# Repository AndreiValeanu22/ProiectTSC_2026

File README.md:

# InkTime – Proiect TSC 2026

## Rezumat

Acest depozit conține schematica nativă, placa de circuit imprimat, livrabilele de manufacturare, materialele mecanice parțiale și documentația vizuală pentru dispozitivul **InkTime**, aliniate structurii cerute în ghidul de proiect de pe [OCW – Proiect 2026](https://ocw.cs.pub.ro/courses/tsc/proiect2026).

## Galerie imagini

Capturile de mai jos sunt versiunile din directorul `Images/` și se afișează direct în pagina README pe GitHub.

### Schematică (două zone)

### Placă de circuit imprimat

### Previzualizări 3D

## Conformitate cu structura de încărcare (OCW)

| Cerință OCW | Conținut în acest depozit |
|-------------|---------------------------|
| `Hardware/` – schematic `.sch` | `ProjectTSCEtapa1.sch` |
| `Hardware/` – placă `.brd` | `InkTime v6_PCB_Partea2.brd` |
| `Hardware/` – print schematic `.pdf` | `InkTime_Schematic.pdf` (compus din capturile din `Images/`) |
| `Manufacturing/` – `gerbers.zip` | `gerbers.zip` (vezi secțiunea *Gerber și export CAM*; include cupru/profil/găuri din `.brd` și, opțional, straturi complete din `fusion_export/`) |
| `Manufacturing/` – BOM `.bom` | `InkTime.bom` |
| `Manufacturing/` – Pick&Place `.cpl` | `InkTime.cpl` |
| `Mechanical/` – ansamblu 3D | `ProjectTSCEtapa1.f3z`, `InkTime_Case.f3z`, modele `.STEP` pentru componente, `InkTime v6_PCB_Partea2.3mf` (vezi secțiunea *Modelare 3D*) |
| `Images/` | Randări și capturi (PCB, schematic, previzualizări 3D) |
| `LICENSE`, `README.md` | Prezente |

### Fișierul `InkTime.fbrd` din `Hardware/`

`InkTime.fbrd` este **fișierul de referință** furnizat prin arhiva OCW pentru recomandări de amplasament mecanic; **nu** înlocuiește proiectul de placă editabil. Proiectul de placă livrat pentru evaluare este `InkTime v6_PCB_Partea2.brd`. Fișierul `InkTime.fbrd.brd`, care genera confuzie în review (nu corespundea unui flux clar schematic → placă), a fost **eliminat** din depozit.

## Structura directoarelor

- `Hardware/` – schematic, placă, PDF-ul schemei.
- `Manufacturing/` – `gerbers.zip`, `InkTime.bom`, `InkTime.cpl`, directorul `fusion_export/` pentru exportul CAM din Fusion (vezi mai jos).
- `Mechanical/` – proiecte Fusion (`.f3z`), model 3MF al PCB-ului, modele STEP pentru componente (ex.: conector USB-C, celulă baterie).
- `Images/` – capturi pentru documentație și pentru compunerea PDF-ului schemei.
- `tools/` – scriptul de generare a livrabilelor de manufacturare și a PDF-ului schemei.

## Gerber și export CAM (cerință OCW)

Conform [ghidului de proiect OCW](https://ocw.cs.pub.ro/courses/tsc/proiect2026), arhiva **`gerbers.zip`** trebuie să conțină setul de fișiere Gerber/Excellon folosit la producție (cupru pe toate straturile, mască, pastă, serigrafie, profil, găuri), generate de obicei prin **CAM Processor** din Fusion Electronics, cu fișierul de reguli DRC indicat la curs.

### Cum obții un `gerbers.zip` complet

1. În **Fusion Electronics**, deschide placa și rulează exportul Gerber/Drill conform [tutorialului OCW pentru Gerber](https://ocw.cs.pub.ro/courses/tsc/proiect2026) (meniul de generare CAM din documentația cursului).
2. Copiază **toate** fișierele rezultate (`.gbr`, `.gtl`, `.gbl`, `.gts`, `.gbs`, `.gtp`, `.gko`, `.drl` etc.) în directorul  
   **`Manufacturing/fusion_export/`** din acest depozit (poți păstra denumirile implicite ale Fusion).
3. Din rădăcina depozitului rulează:  
   `python tools/build_ocw_deliverables.py`  
   Scriptul construiește `gerbers.zip` astfel: **mai întâi** include tot ce se află în `fusion_export/`; **apoi** completează doar fișierele lipsă (ex.: straturi de cupru/profil/găuri) din parsarea XML a fișierului `.brd`, dacă Fusion nu a emis deja un fișier cu același nume. Astfel, după ce plasezi exportul CAM, arhiva reflectă **prioritar** setul oficial Fusion, aliniat cerințelor OCW.

Dacă `fusion_export/` este gol, arhiva conține doar livrabilele derivate automat din `.brd` (util pentru verificare rapidă, fără mască/pastă/silk explicite).

## Diagramă bloc (arhitectură hardware)

```mermaid
flowchart LR
  subgraph Alimentare
    USB[USB-C + protecție ESD]
    BAT[Baterie Li-ion]
    IC1[BQ25180 – încărcare]
    IC9[RT6160 – buck-boost]
  end
  subgraph Aplicație
    U1[nRF52840]
    ANT[Antenă 2,45 GHz]
    J3[Conector e-paper]
    IC3[BMA423 – IMU]
    IC4[DRV2605 – driver haptic]
    U2[MAX17048 – fuel gauge]
  end
  USB --> U1
  BAT --> IC1
  IC1 --> U2
  IC9 --> U1
  U1 --> ANT
  U1 --> J3
  U1 --> IC3
  U1 --> IC4
  U1 --> U2
```

## Descriere hardware (rezumat funcțional)

Microcontrolerul principal **nRF52840** (U1) asigură procesarea, conectivitatea **Bluetooth Low Energy** prin pinul dedicat de RF către antena Johanson, interfața **USB** (D+/D−) pentru programare și alimentare de la port, un magistrală **I²C** comună pentru senzori și periferice (încărcător BQ25180, convertoare, MAX17048, BMA423, DRV2605), precum și un port **SPI** (semnalele `SCK` / `MOSI` și liniile de control) către conectorul **Molex 503480-2400** (J3) al afișajului e-paper. Lanțul de alimentare include încărcarea bateriei (IC1), monitorizarea celulei (U2) și reglarea tensiunii de sistem (IC9), conform schemei `ProjectTSCEtapa1.sch`.

## BOM orientativ (module principale)

Tabelul de mai jos indică **componente-reper**; pentru lista completă a pieselor și a footprint-urilor folosiți `Manufacturing/InkTime.bom` (regenerabil). Linkurile către JLCPCB folosesc căutarea după cod articol; datasheet-urile sunt la producător.

| Rol | Piesă (din schemă) | Căutare JLCPCB | Datasheet |
|-----|-------------------|----------------|-----------|
| MCU + radio BLE | nRF52840 (U1) | [Căutare „nRF52840”](https://jlcpcb.com/parts/componentSearch?searchTxt=nRF52840) | [Nordic Semiconductor](https://www.nordicsemi.com/products/nrf52840) |
| Încărcare baterie | BQ25180YBGR (IC1) | [Căutare „BQ25180”](https://jlcpcb.com/parts/componentSearch?searchTxt=BQ25180) | [Texas Instruments](https://www.ti.com/product/BQ25180) |
| Buck-boost | RT6160AWSC (IC9) | [Căutare „RT6160”](https://jlcpcb.com/parts/componentSearch?searchTxt=RT6160) | [Richtek](https://www.richtek.com/) |
| IMU | BMA423 (IC3) | [Căutare „BMA423”](https://jlcpcb.com/parts/componentSearch?searchTxt=BMA423) | [Bosch Sensortec](https://www.bosch-sensortec.com/media/datasheets/bst-bma423-ds000.pdf) |
| Fuel gauge | MAX17048G+T10 (U2) | [Căutare „MAX17048”](https://jlcpcb.com/parts/componentSearch?searchTxt=MAX17048) | [Analog Devices](https://www.analog.com/en/products/max17048.html) |
| Driver haptic | DRV2605YZFR (IC4) | [Căutare „DRV2605”](https://jlcpcb.com/parts/componentSearch?searchTxt=DRV2605) | [Texas Instruments](https://www.ti.com/product/DRV2605) |
| Protecție USB | USBLC6-2SC6Y (D8) | [Căutare „USBLC6”](https://jlcpcb.com/parts/componentSearch?searchTxt=USBLC6-2SC6Y) | [STMicroelectronics](https://www.st.com/en/protection-ics/usblc6-2sc6y.html) |
| Conector e-paper | 503480-2400 (J3) | [Căutare „503480-2400”](https://jlcpcb.com/parts/componentSearch?searchTxt=503480-2400) | [Molex – căutare serie](https://www.molex.com/molex/products/search?q=503480-2400) |

## Alocare funcțională a pinilor nRF52840 (U1)

Tabelul rezumă legături **esențiale** extrase din `ProjectTSCEtapa1.sch`; pentru decodarea completă a pad-urilor BGA consultați PDF-ul schemei și fișierul `.sch`.

| Funcțiune | Pin GPIO / dedicat (etichetă în schemă) | Observații |
|-----------|----------------------------------------|-------------|
| USB date | `D+`, `D−` | Stivă USB 2.0 integrată în nRF52840 |
| Alimentare USB | `VBUS` | Detecție / alimentare de la conector |
| Depanare SWD | `SWDIO`, `SWDCLK` | Programare și debug |
| Reset | `P0.18` (RESET) | Linie de reset a sistemului |
| RF antenă | `ANT` | Conexiune la rețeaua de adaptare și antenă 2,45 GHz |
| SPI e-paper – ceas | `P0.02` | Semnal `SCK` |
| SPI e-paper – date | `P0.03` | Semnal `MOSI` |
| E-paper – selecție | `P0.05` | `EPD_CS` |
| E-paper – control | `P0.15`, `P0.16`, `P0.17` | Respectiv `EPD_DC`, `EPD_RST`, `EPD_BUSY` |
| I²C periferice | `P0.06` (SDA), `P0.07` (SCL) | Magistrală partajată (încărcător, IMU, gauge, DRV2605 etc.) |
| Întreruperi IMU | `P0.08`, `P1.08` | `IMU_INT1`, `IMU_INT2` |
| Cristal HF | `XC1`, `XC2` | Oscilator 32 MHz pentru radio |

## Justificări tehnice și răspuns la observațiile din review

Secțiunea următoare documentează, în mod explicit, starea **ERC/DRC**, limitările la **modelarea 3D** și, pentru transparență, **via stitching** (ce apare concret în layout) versus **via fencing** (definiție de referință din documentație / curs).

### Schematică și ERC (Electrical Rule Check)

Schema electrică este **funcțional completă** în sensul fluxurilor de alimentare, de date și de interfețe prevăzute de tema InkTime. La rularea **ERC** în mediul Autodesk Fusion / Eagle, rezultatul curent este **0 erori** și **44 avertismente**.

În cadrul laboratorului a fost comunicat faptul că, pentru această temă, **ordinul de mărime a avertismentelor ERC** se situează în mod tipic în jurul valorii de **40** (alți colegi au raportat, de exemplu, **41** de avertismente). În evoluția propriului proiect, au fost înregistrate **43**, apoi **44** de avertismente, după ajustări minore de bibliotecă și de etichetare. Variația cu **una–două unități** față de media grupei se încadrează, din perspectivă inginerească, în **aceeași clasă de severitate**: majoritatea mesajelor sunt **neblocante** (ex.: atribute de catalog incomplete, recomandări de denumire, conexiuni marcate ca „not connected” acolo unde pachetul o permite, sau reguli conservative ale verificatorului). **Nu au fost ignorate erori ERC critice**; avertismentele rămân documentate pentru transparență și pot fi grupate pe categorii (alimentări, biblioteci online, NC) într-o iterație ulterioară de curățare a schemei, fără a altera topologia electrică aprobată.

### Placă (PCB) și DRC (Design Rule Check)

Verificarea **DRC** cu setul de reguli indicat în cadrul cursului raportează, în stadiul curent al plăcii, următoarele categorii (valorile reflectă ultima centralizare folosită în review):

| Categorie DRC | Număr de încălcări | Interpretare sumară |
|-----------------|-------------------:|------------------------|
| Overlap | 65 | Suprapuneri în principal între **pad-uri / pastile de pastă / zone fine** la densitate mare (capsule 0201, sub BGA), uneori exacerbate de toleranțele stricte ale fișierului de reguli. |
| Drill clearance | 3 | Spațiere insuficientă față de **gaură / via** în câteva zone critice. |
| Clearance (cupru) | 14 | Violări de **distanță minimă între obiecte de cupru** (trasee, poligoane, keepout), inclusiv zone cu geometrie compresată. |
| Board outline clearance | 2 | Obiecte apropiate de **conturul mecanic** al plăcii (inclusiv în proximitatea decupărilor pentru antenă sau a alinierii mecanice cu carcasa). |
| Air wires | 26 | Conexiuni **nerealizate complet** în editor (rutare incompletă). |

**Poziția de proiectare.** Eliminarea completă a acestor observații ar impune, în multe locuri, **relocări majore de componente**, subțierea suplimentară a traseelor sub pragul recomandat pentru **putere (0,3 mm)** sau relaxarea keepout-ului antenei, ceea ce contravine obiectivelor de **fiabilitate** și de **conformitate RF** din temă. În practică, **corectarea iterativă** a suprapunerilor și a clearance-urilor devine rapid **neconvexă**: fiecare mică mutare propagă noi conflicte în zonele BGA și în coridorul USB–butoane. Din acest motiv, un subset de încălcări este **acceptat temporar** ca **datorie tehnică documentată**, iar remedierea completă este planificată prin: (1) relaxarea controlată a unor reguli doar acolo unde cursul permite explicit excepții (ex.: note OCW privind anumite dimensionări); (2) **finalizarea rutării** pe straturi interioare și prin optimizarea ordinii de fan-out de sub BGA; (3) revizuirea **stitching**-ului de masă acolo unde pad-urile intră în conflict mecanic cu plasamentul via-urilor.

**Airwires (26).** Menținerea concomitentă a **grosimilor de alimentare**, a **izolației** față de planurile de masă și a **accesului mecanic** (USB, butoane, conector e-paper) limitează numărul de canale de rutare disponibile; unele net-uri rămân astfel **intenționat neînchise** în editor până la o rundă dedicată de **rip-up / re-route**, pentru a nu compromite traseele deja validate din punct de vedere al curentului și al integrității semnalului.

### Modelare 3D și ansamblu STEP unificat

Conform cerințelor OCW, livrabilul ideal include un **STEP unificat** (vedere explodată sau ansamblu complet: PCB + baterie + display + carcasă). În acest depozit, **acest fișier unificat lipsește**.

### Via stitching și via fencing (clarificare pentru acest layout)

În documentație apar adesea împreună **via stitching** și **via fencing** (*via shielding*). În **proiectul InkTime**, ceea ce apare **concret** în placă sunt în primul rând **vias care leagă rețeaua de masă (`GND`) între straturi fizice diferite** (de exemplu cupru pe **Top**, plan de masă pe stratul interior denumit în fișier **Route2**, cupru pe **Bottom**). Acest comportament intră la **via stitching**: **același net electric** (masă) este „cusut” **vertical** prin vias între **layere cu denumiri diferite** în editor. **Nu** este necesar ca două straturi să aibă **același nume** în fișierul `.brd`; este necesar ca **același potențial de referință** să fie continuu între straturi, ceea ce reduce impedanța de masă și ajută la disiparea termică. Referință: [Autodesk – Understanding the Power of Stitching Vias in PCB Design](https://www.autodesk.com/products/fusion-360/blog/understanding-the-power-of-via-stitching-in-pcb-design/).

**Via fencing** (sau *via shielding*) desemnează, în literatură, **rânduri de vias** plasate **de-a lungul unui traseu** sau în jurul unei zone **RF**, pentru ecranare EMI — geometria urmează **linia semnalului**, nu umplerea unui poligon de masă. Definiție și contrast formal: [Altium – Via Stitching & Via Shielding](https://www.altium.com/documentation/altium-designer/pcb/via-stitching-via-shielding).

| Aspect | Via stitching | Via fencing (shielding) |
|--------|----------------|-------------------------|
| Aranjament | Grilă / rețea pe zone mari de cupru (masă) | Rând(uri) paralele, urmărind traseul sau perimetrul |
| Obiect leagat | **Același net** (ex. `GND`) pe **straturi diferite** | Traseu sau zonă sensibilă (ex. RF), cu gard de referință |
| Confuzie frecventă | Nu înseamnă „două layere cu același nume în Eagle” | Nu este același lucru cu un **via obișnuit** care doar traversează placa între două trasee de semnal |
| În proiectul InkTime | **Da**, prin **vias de continuitate pentru masă** între straturi (GND între Top / Route2-GND / Bottom etc.). | **Nu este documentat aici** ca „gard” dedicat de vias pe conturul fiecărui traseu RF; zona antenă este tratată în primul rând prin **keepout** și rutare conform temei; fencing-ul rămâne **reper de curs** pentru design RF avansat. |

**Rezumat:** *stitching* = **cusătură verticală a masei** între layere; *fencing* = **gard** pe lângă traseu; în acest depozit, **afirmația verificabilă** este cea despre **stitching-ul de masă**; **fencing-ul strict** este explicat pentru **comparare**, nu ca să se presupună automat același nivel de implementare ca în exemplele CAD din linkuri.

## Modelare 3D (ansamblu complet)

Ansamblul explodat complet (PCB + baterie + display + carcasă), în format **STEP** unificat, **nu este inclus** momentan. Depozitul conține, pentru continuitate:

- proiecte Fusion (`ProjectTSCEtapa1.f3z`, `InkTime_Case.f3z`);
- export 3MF al PCB-ului cu componente (`InkTime v6_PCB_Partea2.3mf`);
- modele **STEP** pentru subansamble și componente (denumiri derivate din catalog; consultați tabelul de mai jos).

| Fișier | Rol presupus în proiect |
|--------|-------------------------|
| `KH-TYPE-C-16P--3DModel-STEP-269445.STEP` | Model 3D conector USB-C |
| `EVP-AKE31A--3DModel-STEP-56544.STEP` | Model 3D baterie / celulă (EVP-AKE31A) |
| `5034802400--3DModel-STEP-56544.STEP` | Model 3D componentă suplimentară (cod producător) |
| `InkTime v6_PCB_Partea2.3mf` | PCB cu componente (3MF) |
| `ProjectTSCEtapa1.f3z`, `InkTime_Case.f3z` | Proiecte Fusion (ansamblu parțial / carcasă) |

## Note de proiectare și decizii documentate

### Ajustări la nivelul butoanelor

Amplasamentul și geometria **butoanelor** au fost **revizuite incremental** pe stratul de placă, în corelație cu recomandările mecanice din materialele OCW, cu scopul de a **atenua conflictele dimensionale** și de a **reduce severitatea unor erori raportate de DRC** (ex.: depășiri de contur sau interferențe cu zonele de toleranță ale mufei USB-C). Modificările au fost limitate la domeniul necesar menținerii alinierii funcționale cu carcasa, fără a altera schema logică a sistemului.

### Rutare incompletă (airwires)

Procesul de rutare este **în desfășurare**: în stadiul curent al plăcii există **douăzeci și șase de conexiuni nerealizate complet** (afișate de editor ca *airwires*). Cauza principală este **densitatea foarte ridicată** a interconexiunilor în proximitatea circuitelor integrate în capsulă fină (inclusiv sub zona BGA), coroborată cu **restricții severe de spațiu** pe straturile exterioare și cu necesitatea respectării lățimilor minime pentru alimentare și a keepout-ului antenei. Detalii suplimentare și legătura cu raportul DRC se găsesc în secțiunea *Placă (PCB) și DRC*.

## Note de proiect (PCB)

- Patru straturi: Top și Bottom pentru semnale, **Route2** ca plan de masă, **Route15** ca plan de alimentare (conform denumirilor din fișierul `.brd`).
- Trasee de putere: **0,3 mm**; semnale: **minimum 0,15 mm**.
- Antenă la marginea plăcii, cu **keepout** (fără cupru) pe straturile relevante.
- Condensatoare de decuplare cât mai aproape de pini de alimentare.
- Componente plasate exclusiv pe **TOP**.
- **Via stitching** (vias pentru **GND** între **straturi fizice diferite**; layerele nu trebuie să aibă același nume în `.brd`), conform secțiunii dedicate; **via fencing** strict este doar **explicat** acolo, nu echivalat cu simplele vias de masă.

## Rezumat numeric ERC / DRC

| Verificare | Rezultat |
|------------|----------|
| ERC | **0 erori**, **44 avertismente** |
| DRC – Overlap | **65** |
| DRC – Drill clearance | **3** |
| DRC – Clearance (cupru) | **14** |
| DRC – Board outline clearance | **2** |
| DRC – Air wires | **26** |

Valorile trebuie re-verificate după fiecare modificare a plăcii sau după re-exportul CAM.

## Plan de verificare

- ERC: gruparea avertismentelor pe categorii (bibliotecă, NC, alimentări) și eliminarea celor care nu afectează funcția.
- DRC cu fișierul de reguli OCW; iterare pe **overlap** și **clearance** acolo unde nu se sacrifică RF sau puterea.
- Verificare keepout în zona antenei; eventual **via fencing** dedicat doar dacă se adoptă explicit în layout (reper RF din curs).
- Verificare rutare de putere (0,3 mm) și continuitate plan de masă (**via stitching**).
- Regenerare livrabile: `python tools/build_ocw_deliverables.py`.

## Regenerarea livrabilelor

Din rădăcina depozitului, cu Python 3 și pachetele `gerbonara`, `reportlab`, `pillow` instalate. După ce ai plasat exportul CAM în `Manufacturing/fusion_export/`, rulează:

```bash
python tools/build_ocw_deliverables.py
```

Comanda actualizează `InkTime.bom`, `InkTime.cpl`, `InkTime_Schematic.pdf` și reconstruiește `gerbers.zip` conform regulilor de fuziune descrise mai sus.

## Licență

Vezi `LICENSE` (MIT).

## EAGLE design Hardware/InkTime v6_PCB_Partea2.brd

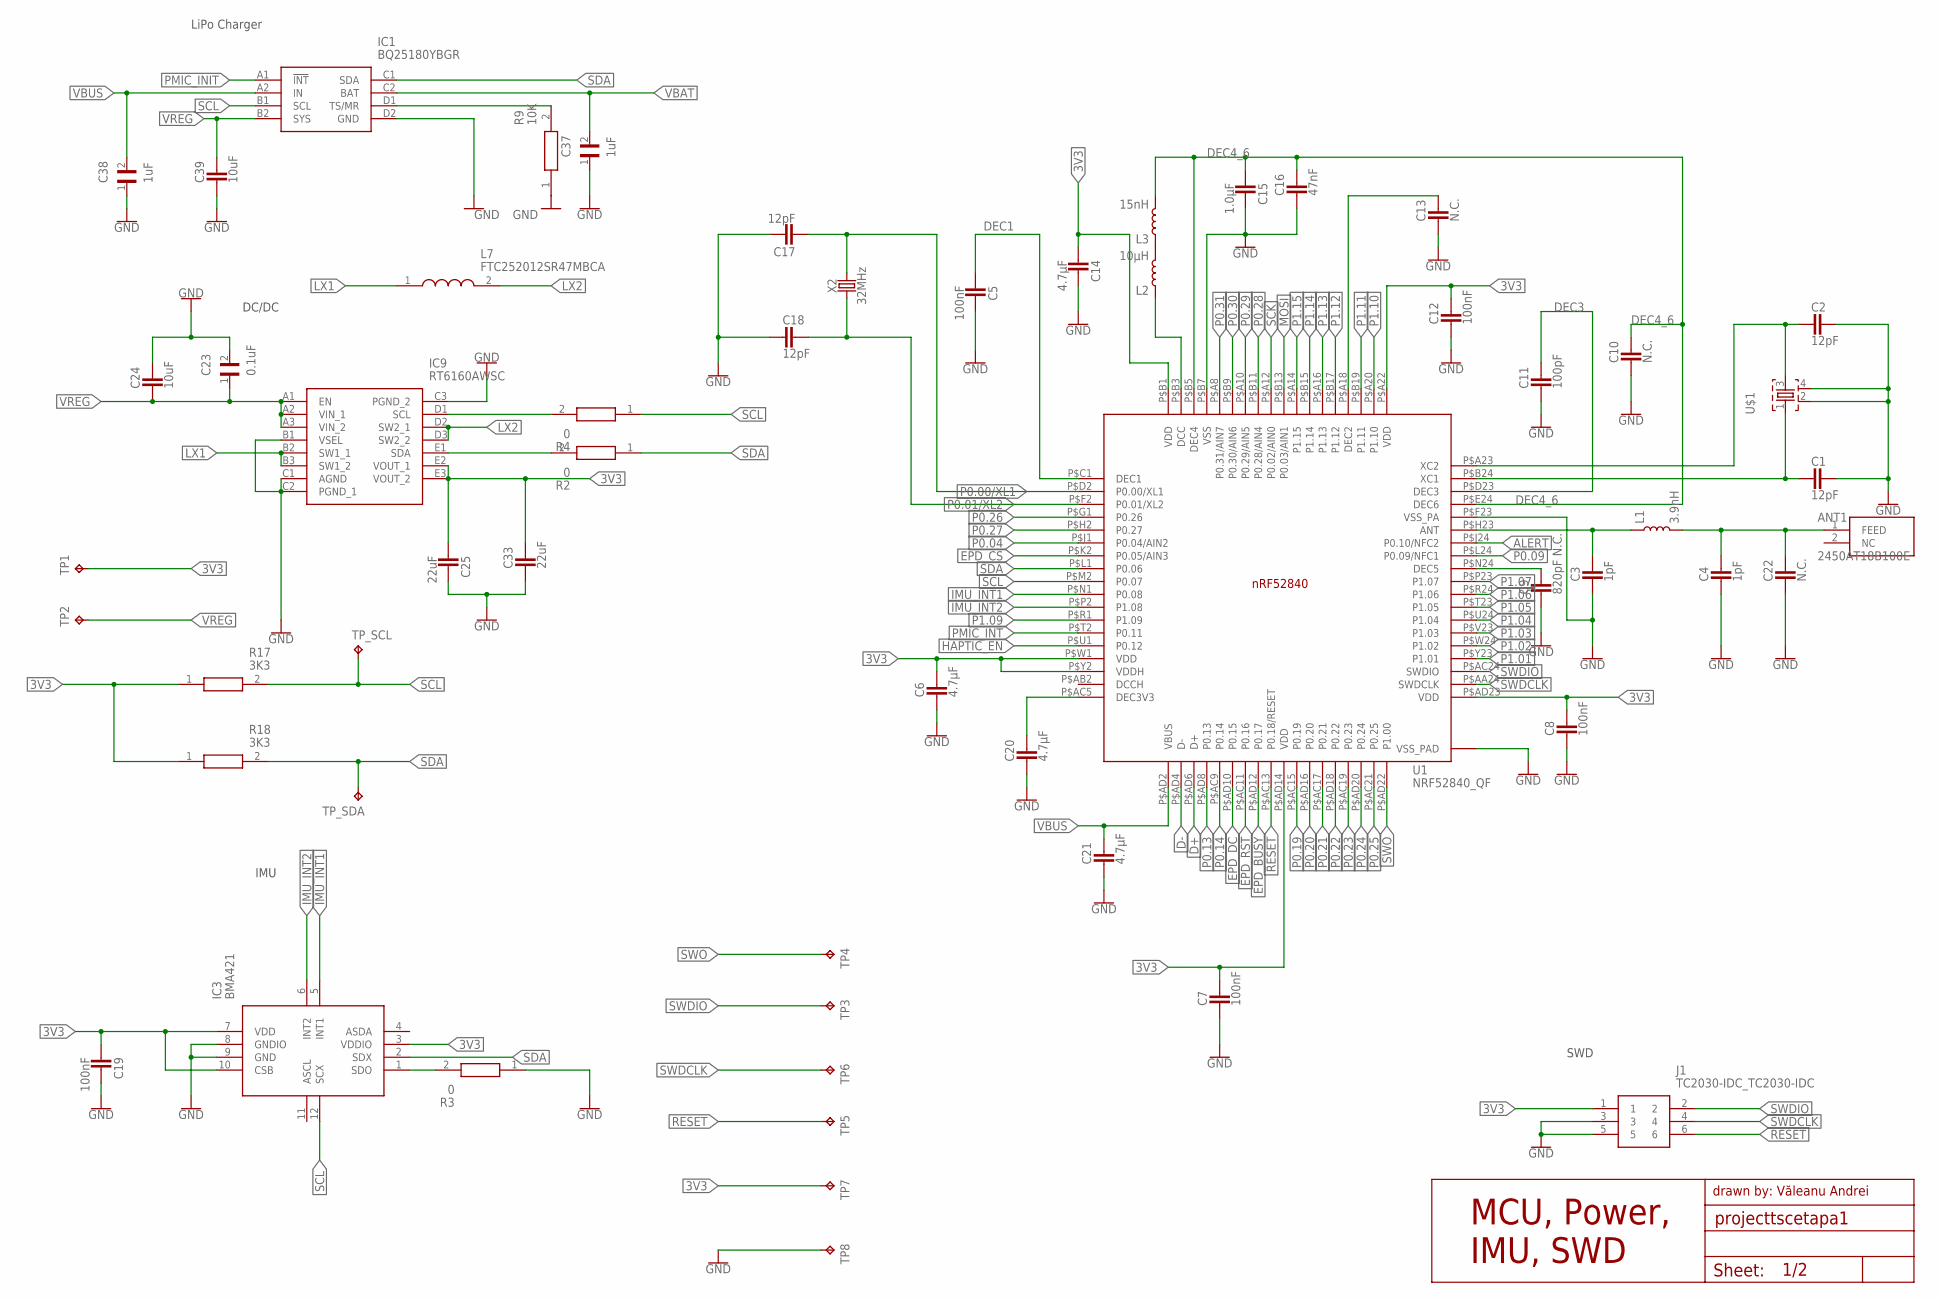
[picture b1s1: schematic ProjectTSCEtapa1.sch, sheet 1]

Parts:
ANT1: 2450AT18B100E; 2450AT18B100E_ANTC3216X140N
C1, C2, C17, C18: 12pF; CAPC1005X60
C3, C4: 1pF; CAPC1005X60
C5, C7, C8, C12, C19: 100nF; CAPC1005X60
C6, C14, C20, C21: 4.7μF; CAPC1005X60
C9: 820pF N.C.; CAPC1005X60
C10, C13, C22: N.C.; CAPC1005X60
C11: 100pF; CAPC1005X60
C15: 1.0μF; CAPC1005X60
C16: 47nF; CAPC1005X60
C23: 0.1uF; GRM011R60J152KE01L_1_0201
C24, C39: 10uF; CAPC1005X60
C25, C33: 22uF; CAPC1005X60
C37, C38: 1uF; GRM011R60J152KE01L_1_0201
IC1: BQ25180YBGR; BQ25180YBGR_BGA8C40P2X4_100X155X50
IC3: BMA421; BMA423_BMA423
IC9: RT6160AWSC; RT6160AWSC_BGA15C40P3X5_140X230X60
J1: TC2030-IDC_TC2030-IDC; TC2030-IDC_TC2030IDC
L1: 3.9nH; 0805-WIDE
L2: 10μH; 0805-WIDE
L3: 15nH; 0805-WIDE
L7: FTC252012SR47MBCA; MLP2016SR47MT0S1_INDC2016X100N
R2, R3, R4: 0; CPF0201D7K68C1_0201
R9: 10K; CPF0201D7K68C1_0201
R17, R18: 3K3; CPF0201D7K68C1_0201
TP1, TP2, TP3, TP4, TP5, TP6, TP7, TP8: HECTOR_WATCH_1_TPTP20R; HECTOR_WATCH_1_TP20R
TP_SCL: HECTOR_WATCH_1_TPTP20R; HECTOR_WATCH_1_TP20R
TP_SDA: HECTOR_WATCH_1_TPTP20R; HECTOR_WATCH_1_TP20R
U1: NRF52840_QF; NORDIC_NRF_4_AQFN50P700X700X85_HS-74N
U$1: NORDIC_NRF_XTAL_32MHZ; NORDIC_NRF_BT-XTAL_2016_N
X2: 32MHz; CRYSTAL-SMD-2.0X1.6MM

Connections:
3V3: C6.1, C7.1, C8.1, C12.1, C14.2, C19.2, C25.2, C33.1, IC3.3 (VDDIO), IC3.7 (VDD), IC3.10 (CSB), IC9.E2 (VOUT_1), IC9.E3 (VOUT_2), J1.1, R17.1, R18.1, TP1.TP, TP7.TP, U1.P$A22 (VDD), U1.P$AD14 (VDD), U1.P$AD23 (VDD), U1.P$B1 (VDD), U1.P$W1 (VDD), U1.P$Y2 (VDDH); also elsewhere on the board
ALERT: U1.P$J24 (P0.10/NFC2); also elsewhere on the board
D+: U1.P$AD6 (D+); also elsewhere on the board
D-: U1.P$AD4 (D-); also elsewhere on the board
DEC1: C5.2, U1.P$C1 (DEC1)
DEC3: C11.1, U1.P$D23 (DEC3)
DEC4_6: C10.1, C15.2, C16.1, L3.2, U1.P$B5 (DEC4), U1.P$E24 (DEC6)
EPD_BUSY: U1.P$AD12 (P0.17); also elsewhere on the board
EPD_CS: U1.P$K2 (P0.05/AIN3); also elsewhere on the board
EPD_DC: U1.P$AD10 (P0.15); also elsewhere on the board
EPD_RST: U1.P$AC11 (P0.16); also elsewhere on the board
GND: C1.1, C2.1, C3.2, C4.2, C5.1, C6.2, C7.2, C8.2, C9.2, C10.2, C11.2, C12.2, C13.2, C14.1, C15.1, C16.2, C17.1, C18.2, C19.1, C20.2, C21.2, C22.2, C23.2, C24.1, C25.1, C33.2, C37.1, C38.1, C39.2, IC1.D2 (GND), IC3.8 (GNDIO), IC3.9 (GND), IC9.B1 (VSEL), IC9.C1 (AGND), IC9.C2 (PGND_1), IC9.C3 (PGND_2), J1.3, J1.5, R3.1, R9.1, TP8.TP, U1.P$74 (VSS_PAD), U1.P$75 (VSS_PAD), U1.P$76 (VSS_PAD), U1.P$77 (VSS_PAD), U1.P$78 (VSS_PAD), U1.P$79 (VSS_PAD), U1.P$80 (VSS_PAD), U1.P$81 (VSS_PAD), U1.P$82 (VSS_PAD), U1.P$83 (VSS_PAD), U1.P$84 (VSS_PAD), U1.P$85 (VSS_PAD), U1.P$86 (VSS_PAD), U1.P$87 (VSS_PAD), U1.P$88 (VSS_PAD), U1.P$89 (VSS_PAD), U1.P$90 (VSS_PAD), U1.P$B7 (VSS), U1.P$F23 (VSS_PA), U$1.2, U$1.4; also elsewhere on the board
HAPTIC_EN: U1.P$U1 (P0.12); also elsewhere on the board
IMU_INT1: IC3.5 (INT1), U1.P$N1 (P0.08)
IMU_INT2: IC3.6 (INT2), U1.P$P2 (P1.08)
LX1: IC9.B2 (SW1_1), IC9.B3 (SW1_2), L7.1
LX2: IC9.D2 (SW2_1), IC9.D3 (SW2_2), L7.2
MOSI: U1.P$B13 (P0.03/AIN1); also elsewhere on the board
unnamed: IC9.D1 (SCL), R4.2
unnamed: IC9.E1 (SDA), R2.2
unnamed: IC3.1 (SDO), R3.2
unnamed: C3.1, L1.1, U1.P$H23 (ANT)
unnamed: ANT1.1 (FEED), C4.1, C22.1, L1.2
unnamed: IC1.D1 (TS/MR), R9.2
unnamed: C9.1, U1.P$N24 (DEC5)
unnamed: C20.1, U1.P$AC5 (DEC3V3)
unnamed: L2.2, L3.1
unnamed: L2.1, U1.P$B3 (DCC)
unnamed: C13.1, U1.P$A18 (DEC2)
unnamed: C2.2, U1.P$A23 (XC2), U$1.3
unnamed: C1.2, U1.P$B24 (XC1), U$1.1
P0.00/XL1: C17.2, U1.P$D2 (P0.00/XL1), X2.3 (2)
P0.01/XL2: C18.1, U1.P$F2 (P0.01/XL2), X2.1
P0.04: U1.P$J1 (P0.04/AIN2)
P0.09: U1.P$L24 (P0.09/NFC1)
P0.13: U1.P$AD8 (P0.13); also elsewhere on the board
P0.14: U1.P$AC9 (P0.14); also elsewhere on the board
P0.19: U1.P$AC15 (P0.19)
P0.20: U1.P$AD16 (P0.20)
P0.21: U1.P$AC17 (P0.21)
P0.22: U1.P$AD18 (P0.22)
P0.23: U1.P$AC19 (P0.23)
P0.24: U1.P$AD20 (P0.24)
P0.25: U1.P$AC21 (P0.25)
P0.26: U1.P$G1 (P0.26)
P0.27: U1.P$H2 (P0.27)
P0.28: U1.P$B11 (P0.28/AIN4)
P0.29: U1.P$A10 (P0.29/AIN5)
P0.30: U1.P$B9 (P0.30/AIN6)
P0.31: U1.P$A8 (P0.31/AIN7)
P1.01: U1.P$Y23 (P1.01); also elsewhere on the board
P1.02: U1.P$W24 (P1.02); also elsewhere on the board
P1.03: U1.P$V23 (P1.03)
P1.04: U1.P$U24 (P1.04)
P1.05: U1.P$T23 (P1.05)
P1.06: U1.P$R24 (P1.06)
P1.07: U1.P$P23 (P1.07)
P1.09: U1.P$R1 (P1.09)
P1.10: U1.P$A20 (P1.10)
P1.11: U1.P$B19 (P1.11)
P1.12: U1.P$B17 (P1.12)
P1.13: U1.P$A16 (P1.13)
P1.14: U1.P$B15 (P1.14)
P1.15: U1.P$A14 (P1.15)
PMIC_INIT: IC1.A1 (!INT)
PMIC_INT: U1.P$T2 (P0.11)
RESET: J1.6, TP5.TP, U1.P$AC13 (P0.18/RESET)
SCK: U1.P$A12 (P0.02/AIN0); also elsewhere on the board
SCL: IC1.B1 (SCL), IC3.12 (SCX), R4.1, R17.2, TP_SCL.TP, U1.P$M2 (P0.07); also elsewhere on the board
SDA: IC1.C1 (SDA), IC3.2 (SDX), R2.1, R18.2, TP_SDA.TP, U1.P$L1 (P0.06); also elsewhere on the board
SWDCLK: J1.4, TP6.TP, U1.P$AA24 (SWDCLK)
SWDIO: J1.2, TP3.TP, U1.P$AC24 (SWDIO)
SWO: TP4.TP, U1.P$AD22 (P1.00)
VBAT: C37.2, IC1.C2 (BAT); also elsewhere on the board
VBUS: C21.1, C38.2, IC1.A2 (IN), U1.P$AD2 (VBUS); also elsewhere on the board
VREG: C23.1, C24.2, C39.1, IC1.B2 (SYS), IC9.A1 (EN), IC9.A2 (VIN_1), IC9.A3 (VIN_2), TP2.TP

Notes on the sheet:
1/2
Sheet:
MCU, Power, IMU, SWD
drawn by: Văleanu Andrei
LiPo Charger
DC/DC
IMU
SWD

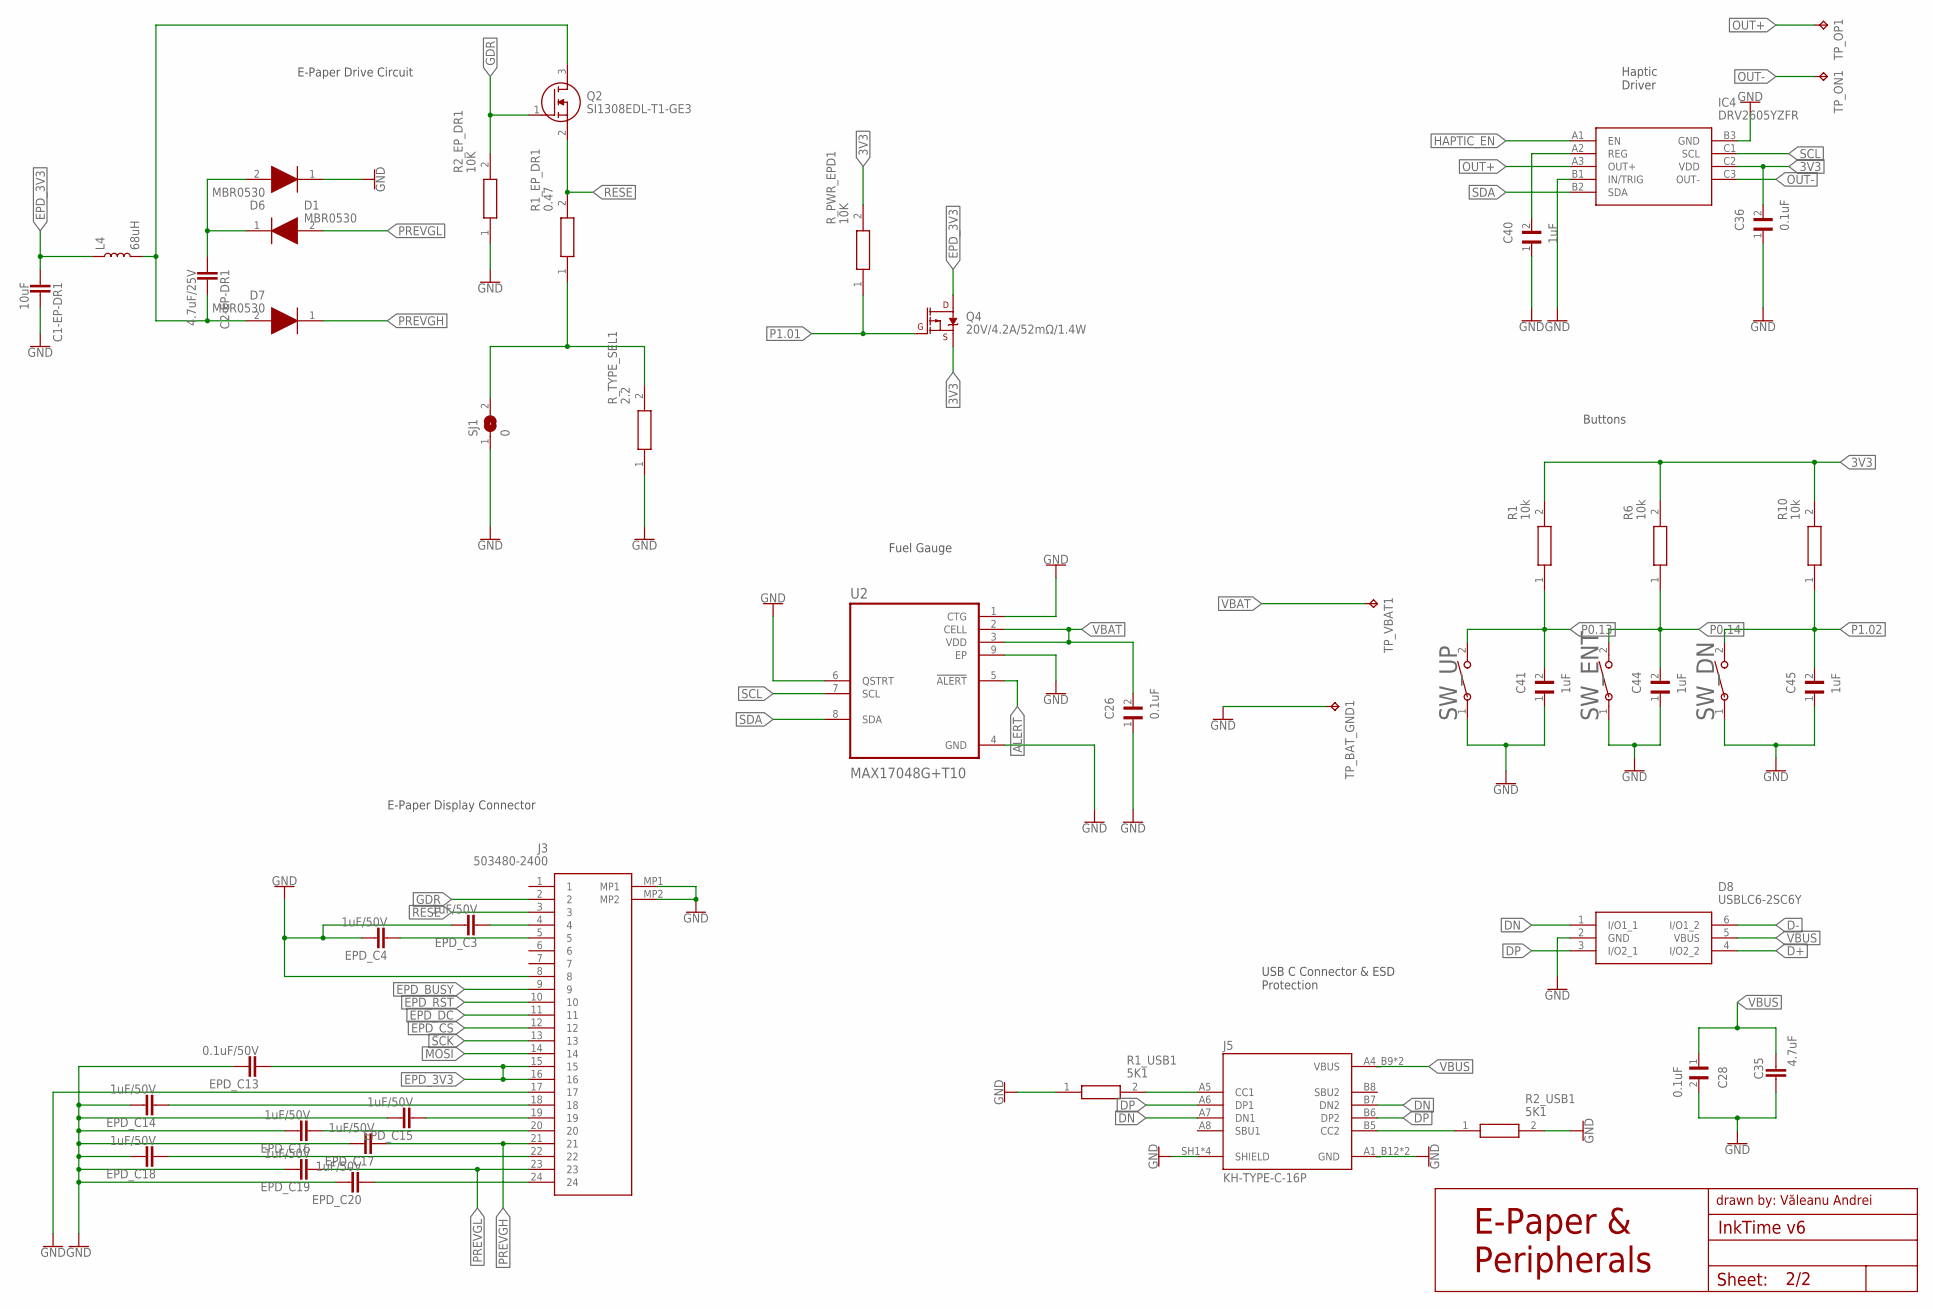
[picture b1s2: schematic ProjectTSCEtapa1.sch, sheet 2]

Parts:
C1-EP-DR1: 10uF; CAPC1005X60
C2-EP-DR1: 4.7uF/25V; CAPC1005X60
C26, C28, C36: 0.1uF; GRM011R60J152KE01L_1_0201
C35: 4.7uF; CAPC1005X60
C40, C41, C44, C45: 1uF; GRM011R60J152KE01L_1_0201
D1, D6, D7: MBR0530; ESP32_C6_LIBRARY_5_SOD3716X135N
D8: USBLC6-2SC6Y; ESP32_C6_LIBRARY_3_SOT95P280X145-6N
EPD_C3, EPD_C4, EPD_C14, EPD_C15, EPD_C16, EPD_C17, EPD_C18, EPD_C19, EPD_C20: 1uF/50V; CAPC1005X60
EPD_C13: 0.1uF/50V; CAPC1005X60
IC4: DRV2605YZFR; DRV2605YZFR_BGA9C50P3X3_144X144X62
J3: 503480-2400; 503480-2400_5034802400
J5: KH-TYPE-C-16P; KH-TYPE-C-16P_KINGHELM_KH-TYPE-C-16P
L4: 68uH; XFL4020
Q2: SI1308EDL-T1-GE3; ESP32_C6_LIBRARY_6_SOT65P210X110-3N
Q4: 20V/4.2A/52mΩ/1.4W; ESP32_C6_LIBRARY_4_ESP32_C6_LIBRARY_4_ESP32_C6_LIBRARY_4_ES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
R1, R6, R10: 10k; CPF0201D7K68C1_0201
R1_EP_DR1: 0.47; CPF0201D7K68C1_0201
R1_USB1, R2_USB1: 5K1; CPF0201D7K68C1_0201
R2_EP_DR1: 10K; CPF0201D7K68C1_0201
R_PWR_EPD1: 10K; CPF0201D7K68C1_0201
R_TYPE_SEL1: 2.2; CPF0201D7K68C1_0201
SJ1: 0; ESP32_C6_LIBRARY_7_JUMPER_SJ
SW_DN: 2025-10-22_07-23-44_LIBRARY_EVP-AKE31ASW_EVP-AKE3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; 2025-10-22_07-23-44_LIBRARY_SW_EVP-AKE31A_PAN
SW_ENT: 2025-10-22_07-23-44_LIBRARY_EVP-AKE31ASW_EVP-AKE3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; 2025-10-22_07-23-44_LIBRARY_SW_EVP-AKE31A_PAN
SW_UP: 2025-10-22_07-23-44_LIBRARY_EVP-AKE31ASW_EVP-AKE3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; 2025-10-22_07-23-44_LIBRARY_SW_EVP-AKE31A_PAN
TP_BAT_GND1: HECTOR_WATCH_1_TPTP20R; HECTOR_WATCH_1_TP20R
TP_ON1: HECTOR_WATCH_1_TPTP20R; HECTOR_WATCH_1_TP20R
TP_OP1: HECTOR_WATCH_1_TPTP20R; HECTOR_WATCH_1_TP20R
TP_VBAT1: HECTOR_WATCH_1_TPTP20R; HECTOR_WATCH_1_TP20R
U2: MAX17048G+T10; ESP32_C6_LIBRARY_SON50P200X200X80-9N

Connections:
3V3: C36.2, IC4.C2 (VDD), Q4.2 (S), R1.2, R6.2, R10.2, R_PWR_EPD1.2; also elsewhere on the board
3V3/1.7D2: C40.2, IC4.A2 (REG)
ALERT: U2.5 (!ALERT); also elsewhere on the board
D+: D8.4 (I/O2_2); also elsewhere on the board
D-: D8.6 (I/O1_2); also elsewhere on the board
DN: D8.1 (I/O1_1), J5.A7 (DN1), J5.B7 (DN2)
DP: D8.3 (I/O2_1), J5.A6 (DP1), J5.B6 (DP2)
EPD_3V3: C1-EP-DR1.2, EPD_C13.2, J3.15, J3.16, L4.P$1 (1), Q4.3 (D)
EPD_BUSY: J3.9; also elsewhere on the board
EPD_CS: J3.12; also elsewhere on the board
EPD_DC: J3.11; also elsewhere on the board
EPD_RST: J3.10; also elsewhere on the board
GDR: J3.2, Q2.1 (G), R2_EP_DR1.2
GND: C1-EP-DR1.1, C26.1, C28.2, C35.2, C36.1, C40.1, C41.1, C44.1, C45.1, D6.1 (K), D8.2 (GND), EPD_C3.1, EPD_C4.1, EPD_C13.1, EPD_C14.1, EPD_C15.1, EPD_C16.1, EPD_C17.1, EPD_C18.1, EPD_C19.1, EPD_C20.1, IC4.B1 (IN/TRIG), IC4.B3 (GND), J3.8, J3.17, J3.MP1, J3.MP2, J5.A1_B12 (GND), J5.A12_B1 (GND), J5.SH1 (SHIELD), J5.SH2 (SHIELD), J5.SH3 (SHIELD), J5.SH4 (SHIELD), R1_USB1.1, R2_EP_DR1.1, R2_USB1.2, R_TYPE_SEL1.1, SJ1.1, SW_DN.1, SW_ENT.1, SW_UP.1, TP_BAT_GND1.TP, U2.1 (CTG), U2.4 (GND), U2.6 (QSTRT), U2.9 (EP); also elsewhere on the board
HAPTIC_EN: IC4.A1 (EN); also elsewhere on the board
MOSI: J3.14; also elsewhere on the board
unnamed: C2-EP-DR1.1, D7.2 (A), L4.P$2 (2), Q2.3 (D)
unnamed: R1_EP_DR1.1, R_TYPE_SEL1.2, SJ1.2
unnamed: C2-EP-DR1.2, D1.1 (K), D6.2 (A)
unnamed: EPD_C3.2, J3.4
unnamed: EPD_C4.2, J3.5
unnamed: EPD_C14.2, J3.18
unnamed: EPD_C15.2, J3.19
unnamed: EPD_C16.2, J3.20
unnamed: EPD_C18.2, J3.22
unnamed: EPD_C20.2, J3.24
unnamed: J5.A5 (CC1), R1_USB1.2
unnamed: J5.B5 (CC2), R2_USB1.1
OUT+: IC4.A3 (OUT+), TP_OP1.TP
OUT-: TP_ON1.TP
P0.13: C41.2, R1.1, SW_UP.2; also elsewhere on the board
P0.14: C44.2, R6.1, SW_ENT.2; also elsewhere on the board
P1.01: Q4.1 (G), R_PWR_EPD1.1; also elsewhere on the board
P1.02: C45.2, R10.1, SW_DN.2; also elsewhere on the board
PREVGH: D7.1 (K), EPD_C17.2, J3.21
PREVGL: D1.2 (A), EPD_C19.2, J3.23
RESE: J3.3, Q2.2 (S), R1_EP_DR1.2
SCK: J3.13; also elsewhere on the board
SCL: IC4.C1 (SCL), U2.7 (SCL); also elsewhere on the board
SDA: IC4.B2 (SDA), U2.8 (SDA); also elsewhere on the board
VBAT: C26.2, TP_VBAT1.TP, U2.2 (CELL), U2.3 (VDD); also elsewhere on the board
VBUS: C28.1, C35.1, D8.5 (VBUS), J5.A4_B9 (VBUS), J5.A9_B4 (VBUS); also elsewhere on the board

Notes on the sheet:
InkTime v6
2/2
Sheet:
E-Paper & Peripherals
drawn by: Văleanu Andrei
E-Paper Drive Circuit
E-Paper Display Connector
Fuel Gauge
USB C Connector & ESD Protection
Buttons
Haptic Driver

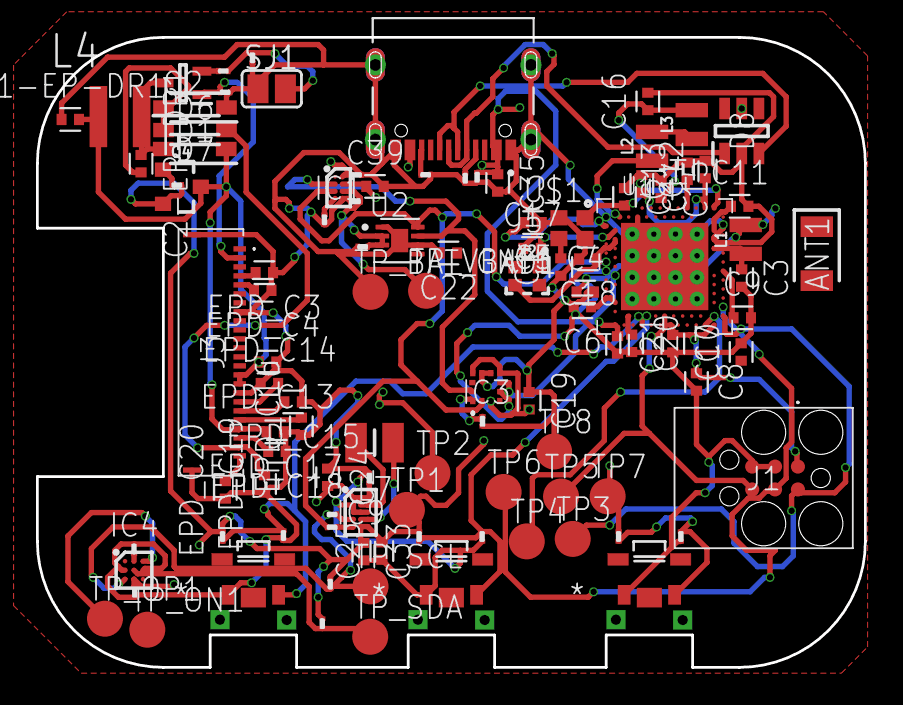
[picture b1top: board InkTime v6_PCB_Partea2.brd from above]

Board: 4 copper layers, 46.0 x 35.0 mm, 105 parts (0 on the bottom side), 68 nets.

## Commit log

2026-04-10 Add hardware, mechanical, manufacturing files
2026-04-10 Finalize repository structure
2026-04-10 Add Images, Manufacturing, and LICENSE
2026-04-16 Align repository with OCW deliverable structure
    Remove confusing InkTime.fbrd.brd; add native .sch/.brd, schematic PDF, gerbers.zip, BOM and CPL; populate Images; add 3MF export and tools/build_ocw_deliverables.py. README documents OCW mapping, pa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
    Made-with: Cursor
2026-04-16 README: gallery, OCW docs, fusion_export merge; extend gerber script
    Add Images to README; document fusion_export CAM workflow; BOM, block diagram, nRF52840 pin summary; merge Fusion exports into gerbers.zip with precedence.
    Made-with: Cursor
2026-04-19 README: ERC/DRC justifications, 3D OCW access, via stitching vs fencing
    Document lab ERC warning band, updated DRC counts from review, DRC remediation limits, 3D STEP gap and OCW download issues, via stitching vs via fencing with references; fix typo semnalele; extend ve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
    Made-with: Cursor
2026-04-19 README: clarify via stitching vs fencing for actual layout
    Document GND vias across differently named layers as stitching; do not claim strict via fencing; fix plan and PCB notes.
    Made-with: Cursor
2026-04-19 README: remove 3D OCW access motivation paragraph
    Made-with: Cursor

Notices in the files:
parts and their libraries:
SparkFun-Coils: Licensing: Creative Commons ShareAlike 4.0 International - https://creativecommons.org/licenses/by-sa/4.0
COPYRIGHT: Copyright (C) 2025 Ultra Librarian. All rights reserved.
